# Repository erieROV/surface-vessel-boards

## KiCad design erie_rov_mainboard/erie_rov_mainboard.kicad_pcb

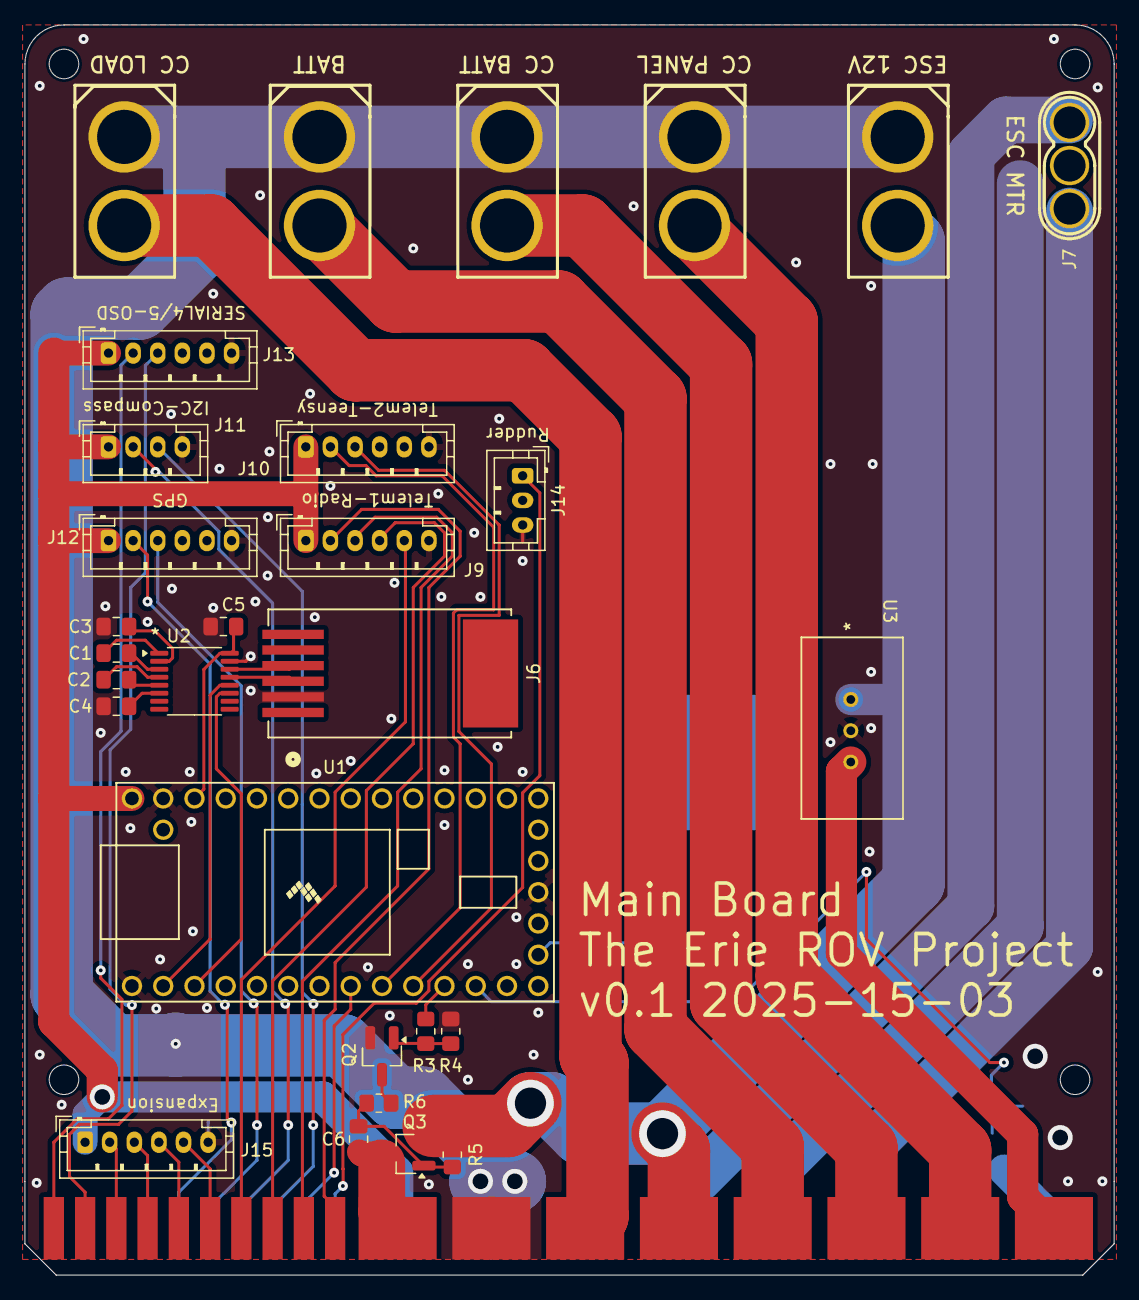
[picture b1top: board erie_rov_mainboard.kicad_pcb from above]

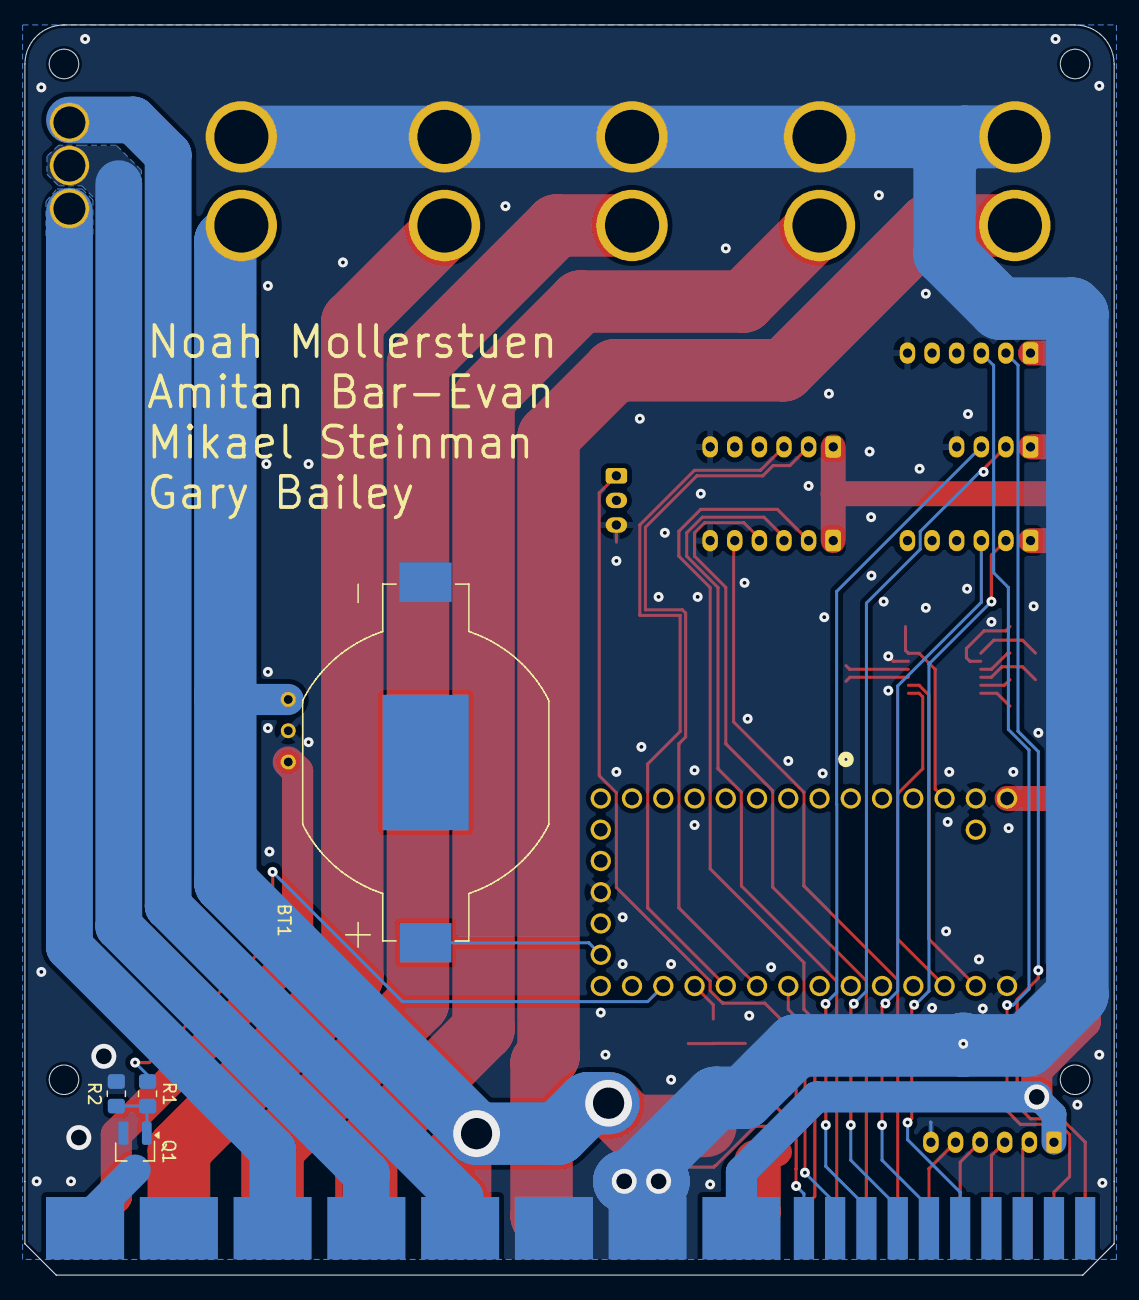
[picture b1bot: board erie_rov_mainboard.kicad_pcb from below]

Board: 2 copper layers, 88.5 x 101.6 mm, 34 parts (4 on the bottom side), 49 nets.

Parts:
BT1: BU2032SM-HD-G; BAT_BU2032SM-HD-G
C1, C2, C3, C4, C5: 0.1uF; C_0805_2012Metric_Pad1.18x1.45mm_HandSolder
C6: 10n; C_0805_2012Metric_Pad1.18x1.45mm_HandSolder
J1: 1761426-1; 1761426_1_CardEdge
J2: BATT; CONN-TH_XT60
J3: CC PANEL; CONN-TH_XT60
J4: CC BATT; CONN-TH_XT60
J5: CC LOAD; CONN-TH_XT60
J6: 855135002; CONN_85513-5002_MOL
J7: ESC MTR; CONN-TH_MR30-M
J8: ESC 12V; CONN-TH_XT60
J9: Telem1-Radio; JST_PH_B6B-PH-K_1x06_P2.00mm_Vertical
J10: Telem2-Teensy; JST_PH_B6B-PH-K_1x06_P2.00mm_Vertical
J11: I2C; JST_PH_B4B-PH-K_1x04_P2.00mm_Vertical
J12: GPS; JST_PH_B6B-PH-K_1x06_P2.00mm_Vertical
J13: SERIAL4/5-OSD; JST_PH_B6B-PH-K_1x06_P2.00mm_Vertical
J14: Rudder; JST_PH_B3B-PH-K_1x03_P2.00mm_Vertical
J15: Expansion; JST_PH_B6B-PH-K_1x06_P2.00mm_Vertical
Q1, Q2: FDV303N; SOT-23_Handsoldering
Q3: AO3401A; SOT-23_Handsoldering
R1, R3: 100; R_0805_2012Metric_Pad1.20x1.40mm_HandSolder
R2, R4, R5: 10K; R_0805_2012Metric_Pad1.20x1.40mm_HandSolder
R6: 1k; R_0805_2012Metric_Pad1.20x1.40mm_HandSolder
U1: Teensy4.0; Teensy40
U2: MAX3232CUE+T; TSSOP-16_4.4x5mm_P0.65mm
U3: TSR 2-2450; TSR 2-2450_TRP

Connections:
5V_AUX: J1.1, U3.3 (+VOUT)
+3.3V: C5.2, U1.31 (3V3), U2.16 (VCC)
+5V: J1.45 (P9), J9.1, J10.1, J11.1, J12.1, J13.1, J15.1, U1.33 (VIN)
+12V: J1.13 (P5), J8.2 (+), Q3.2 (S), R5.1, U3.1 (+VIN)
BATT_CC: J1.7 (P3), J4.2 (+)
BATT_SW: J1.10 (P4), J2.2 (+)
EXP_1: J1.32 (S8), J15.2
EXP_2: J1.31 (S7), J15.3
EXP_3: J1.30 (S6), J15.4
EXP_4: J1.29 (S5), J15.5
GND: BT1.-, C3.2, C4.1, C5.1, J1.19 (P7), J1.48 (P10), J1.51 (P11), J2.1 (-), J3.1 (-), J4.1 (-), J5.1 (-), J6.2, J8.1 (-), J9.6, J10.6, J11.4, J12.6, J13.6, J14.3, J15.6, Q1.2 (S), Q2.2 (S), R2.2, R4.2, U1.1 (GND), U1.17 (GND), U1.32 (GND), U2.15 (GND), U3.2 (GND)
GPS_RX: J1.40 (S16), J12.3
GPS_SCA: J1.42 (S18), J11.3
GPS_SCL: J1.41 (S17), J11.2
GPS_TX: J1.39 (S15), J12.2
LOAD_CC: J1.16 (P6), J5.2 (+)
MTR_B: J1.54 (P12), J7.1
MTR_G: J1.57 (P13), J7.2
MTR_W: J1.60 (P14), J7.3
unnamed: Q1.1 (G), R1.1, R2.1
unnamed: Q2.3 (D), R6.2
unnamed: Q2.1 (G), R3.1, R4.1
unnamed: C6.1, Q3.1 (G), R5.2, R6.1
unnamed: BT1.+, U1.15 (VBAT)
unnamed: C1.2, U2.1 (C1+)
unnamed: C1.1, U2.3 (C1-)
unnamed: C2.2, U2.4 (C2+)
unnamed: C2.1, U2.5 (C2-)
unnamed: J6.3, U2.13 (R1IN)
unnamed: J6.4, U2.14 (T1OUT)
unnamed: C3.1, U2.2 (V+)
unnamed: C4.2, U2.6 (V-)
OSD_RX: J1.33 (S9), J13.3
OSD_TX: J1.34 (S10), J13.2
PNL+: J1.4 (P2), J3.2 (+)
RDR_PWM: J1.44 (S20), J14.1
SCC_RX: U1.2 (0_RX1_CRX2_CS1), U2.12 (R1OUT)
SCC_TX: U1.3 (1_TX1_CTX2_MISO1), U2.11 (T1IN)
STRB_PWM: J1.43 (S19), U1.8 (6_OUT1D)
TELEM1_CTS: J1.27 (S3), J9.4
TELEM1_RTS: J1.28 (S4), J9.5
TELEM1_RX: J1.26 (S2), J9.3
TELEM1_TX: J1.25 (S1), J9.2
TELEM2_RX: J10.3, U1.10 (8_TX2_IN1)
TELEM2_TX: J10.2, U1.9 (7_RX2_OUT1A)
TELEM_GND: J1.66 (P16), Q1.3 (D)
TELEM_SW: R1.2, U1.12 (10_CS_MQSR)
VID_PWR: C6.2, J1.22 (P8), Q3.3 (D)
VTX_SW: R3.2, U1.11 (9_OUT1C)

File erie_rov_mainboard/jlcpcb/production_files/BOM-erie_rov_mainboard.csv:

Comment,Designator,Footprint,LCSC
BATT,"J2,J3,J4,J5,J8",CONN-TH_XT60,C98733
ESC MTR,J7,CONN-TH_MR30-M,C99873
1761426-1,J1,1761426_1_CardEdge,
MAX3232CUE+T,U2,TSSOP-16_4.4x5mm_P0.65mm,
AO3401A,Q3,SOT-23_Handsoldering,
0.1uF,C3,C_0805_2012Metric_Pad1.18x1.45mm_HandSolder,
Rudder,J14,JST_PH_B3B-PH-K_1x03_P2.00mm_Vertical,
Telem2-Teensy,J10,JST_PH_B6B-PH-K_1x06_P2.00mm_Vertical,
Expansion,J15,JST_PH_B6B-PH-K_1x06_P2.00mm_Vertical,
GPS,J12,JST_PH_B6B-PH-K_1x06_P2.00mm_Vertical,
100,R3,R_0805_2012Metric_Pad1.20x1.40mm_HandSolder,
Teensy4.0,U1,Teensy40,
I2C,J11,JST_PH_B4B-PH-K_1x04_P2.00mm_Vertical,
0.1uF,C1,C_0805_2012Metric_Pad1.18x1.45mm_HandSolder,
10K,R5,R_0805_2012Metric_Pad1.20x1.40mm_HandSolder,
Telem1-Radio,J9,JST_PH_B6B-PH-K_1x06_P2.00mm_Vertical,
FDV303N,Q2,SOT-23_Handsoldering,
0.1uF,C5,C_0805_2012Metric_Pad1.18x1.45mm_HandSolder,
10K,R4,R_0805_2012Metric_Pad1.20x1.40mm_HandSolder,
855135002,J6,CONN_85513-5002_MOL,
TSR 2-2450,U3,TSR 2-2450_TRP,
SERIAL4/5-OSD,J13,JST_PH_B6B-PH-K_1x06_P2.00mm_Vertical,
0.1uF,C2,C_0805_2012Metric_Pad1.18x1.45mm_HandSolder,
0.1uF,C4,C_0805_2012Metric_Pad1.18x1.45mm_HandSolder,
BU2032SM-HD-G,BT1,BAT_BU2032SM-HD-G,
10K,R2,R_0805_2012Metric_Pad1.20x1.40mm_HandSolder,
FDV303N,Q1,SOT-23_Handsoldering,
100,R1,R_0805_2012Metric_Pad1.20x1.40mm_HandSolder,
1k,R6,R_0805_2012Metric_Pad1.20x1.40mm_HandSolder,
10n,C6,C_0805_2012Metric_Pad1.18x1.45mm_HandSolder,

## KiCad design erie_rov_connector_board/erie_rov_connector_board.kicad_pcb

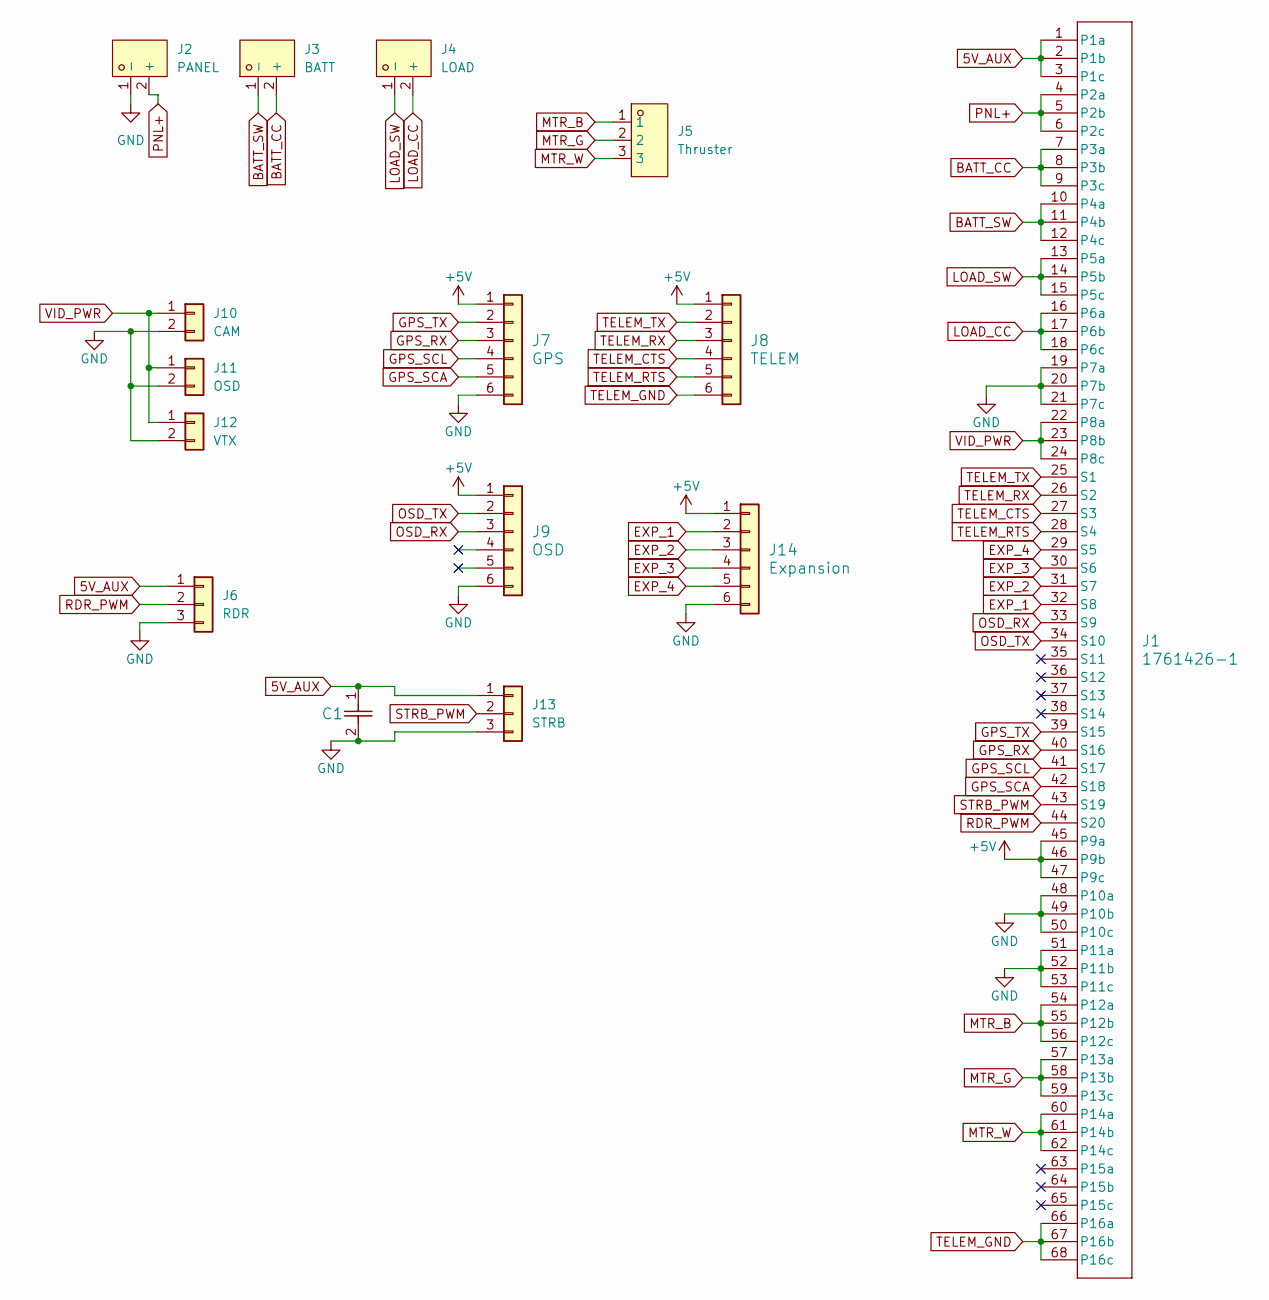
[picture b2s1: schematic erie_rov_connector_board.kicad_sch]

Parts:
C1: 16PK4700MEFC12.5X25; CAP_PK&slash_PZ_12P5X25_LOW_RUB
J1: 1761426-1; 1761426_1
J2: PANEL; CONN-TH_XT60; LCSC Part C98733
J3: BATT; CONN-TH_XT60; LCSC Part C98733
J4: LOAD; CONN-TH_XT60; LCSC Part C98733
J5: Thruster; CONN-TH_MR30-M; LCSC Part C99873
J6: RDR; JST_PH_B3B-PH-K_1x03_P2.00mm_Vertical; MPN B3B-XH-A(LF)(SN); Digi-Key_PN 455-2248-ND
J7: GPS; JST_PH_B6B-PH-K_1x06_P2.00mm_Vertical
J8: TELEM; JST_PH_B6B-PH-K_1x06_P2.00mm_Vertical
J9: OSD; JST_PH_B6B-PH-K_1x06_P2.00mm_Vertical
J10: CAM; JST_PH_B2B-PH-K_1x02_P2.00mm_Vertical; MPN B3B-XH-A(LF)(SN); Digi-Key_PN 455-2248-ND
J11: OSD; JST_PH_B2B-PH-K_1x02_P2.00mm_Vertical; MPN B3B-XH-A(LF)(SN); Digi-Key_PN 455-2248-ND
J12: VTX; JST_PH_B2B-PH-K_1x02_P2.00mm_Vertical; MPN B3B-XH-A(LF)(SN); Digi-Key_PN 455-2248-ND
J13: STRB; JST_PH_B3B-PH-K_1x03_P2.00mm_Vertical; MPN B3B-XH-A(LF)(SN); Digi-Key_PN 455-2248-ND
J14: Expansion; JST_PH_B6B-PH-K_1x06_P2.00mm_Vertical

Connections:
5V_AUX: C1.1, J1.1 (P1a), J1.2 (P1b), J1.3 (P1c), J6.1, J13.1
+5V: J1.45 (P9a), J1.46 (P9b), J1.47 (P9c), J7.1, J8.1, J9.1, J14.1
BATT_CC: J1.7 (P3a), J1.8 (P3b), J1.9 (P3c), J3.2 (+)
BATT_SW: J1.10 (P4a), J1.11 (P4b), J1.12 (P4c), J3.1 (-)
EXP_1: J1.32 (S8), J14.2
EXP_2: J1.31 (S7), J14.3
EXP_3: J1.30 (S6), J14.4
EXP_4: J1.29 (S5), J14.5
GND: C1.2, J1.19 (P7a), J1.20 (P7b), J1.21 (P7c), J1.48 (P10a), J1.49 (P10b), J1.50 (P10c), J1.51 (P11a), J1.52 (P11b), J1.53 (P11c), J2.1 (-), J6.3, J7.6, J9.6, J10.2, J11.2, J12.2, J13.3, J14.6
GPS_RX: J1.40 (S16), J7.3
GPS_SCA: J1.42 (S18), J7.5
GPS_SCL: J1.41 (S17), J7.4
GPS_TX: J1.39 (S15), J7.2
LOAD_CC: J1.16 (P6a), J1.17 (P6b), J1.18 (P6c), J4.2 (+)
LOAD_SW: J1.13 (P5a), J1.14 (P5b), J1.15 (P5c), J4.1 (-)
MTR_B: J1.54 (P12a), J1.55 (P12b), J1.56 (P12c), J5.1
MTR_G: J1.57 (P13a), J1.58 (P13b), J1.59 (P13c), J5.2
MTR_W: J1.60 (P14a), J1.61 (P14b), J1.62 (P14c), J5.3
OSD_RX: J1.33 (S9), J9.3
OSD_TX: J1.34 (S10), J9.2
PNL+: J1.4 (P2a), J1.5 (P2b), J1.6 (P2c), J2.2 (+)
RDR_PWM: J1.44 (S20), J6.2
STRB_PWM: J1.43 (S19), J13.2
TELEM_CTS: J1.27 (S3), J8.4
TELEM_GND: J1.66 (P16a), J1.67 (P16b), J1.68 (P16c), J8.6
TELEM_RTS: J1.28 (S4), J8.5
TELEM_RX: J1.26 (S2), J8.3
TELEM_TX: J1.25 (S1), J8.2
VID_PWR: J1.22 (P8a), J1.23 (P8b), J1.24 (P8c), J10.1, J11.1, J12.1

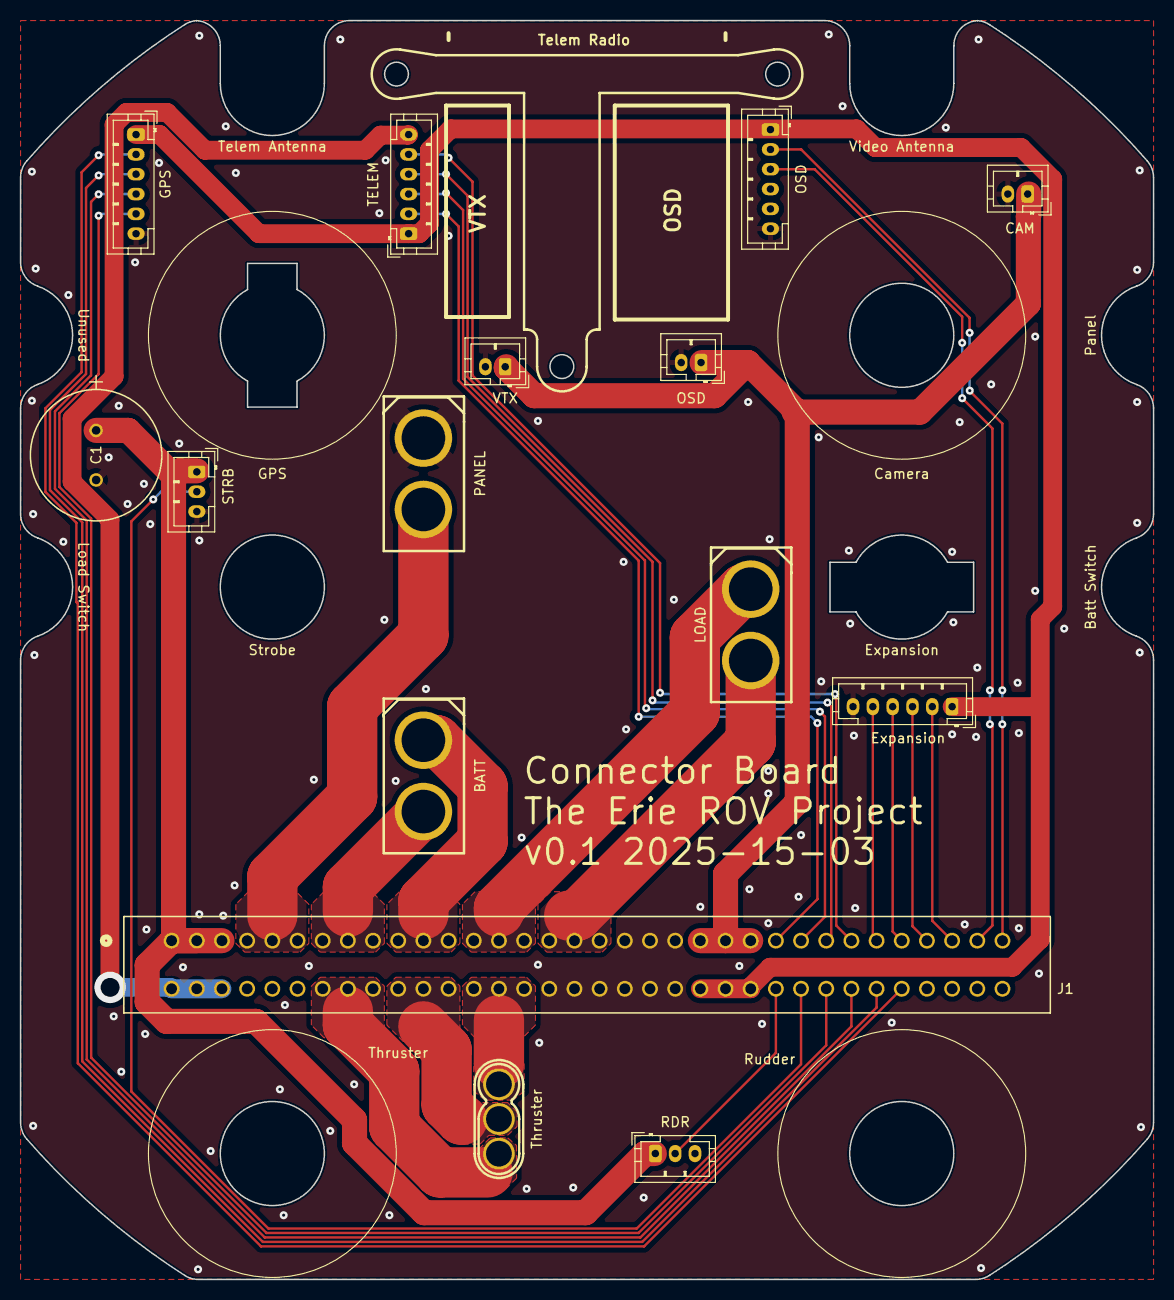
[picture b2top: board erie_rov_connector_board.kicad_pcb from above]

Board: 2 copper layers, 114.3 x 127.0 mm, 15 parts (0 on the bottom side), 29 nets.

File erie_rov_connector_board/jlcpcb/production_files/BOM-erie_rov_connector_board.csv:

Comment,Designator,Footprint,LCSC
PANEL,"J2,J3,J4",CONN-TH_XT60,C98733
Thruster,J5,CONN-TH_MR30-M,C99873
OSD,J9,JST_PH_B6B-PH-K_1x06_P2.00mm_Vertical,
Expansion,J14,JST_PH_B6B-PH-K_1x06_P2.00mm_Vertical,
OSD,J11,JST_PH_B2B-PH-K_1x02_P2.00mm_Vertical,
16PK4700MEFC12.5X25,C1,CAP_PK&slash_PZ_12P5X25_LOW_RUB,
CAM,J10,JST_PH_B2B-PH-K_1x02_P2.00mm_Vertical,
RDR,J6,JST_PH_B3B-PH-K_1x03_P2.00mm_Vertical,
1761426-1,J1,1761426_1,
GPS,J7,JST_PH_B6B-PH-K_1x06_P2.00mm_Vertical,
VTX,J12,JST_PH_B2B-PH-K_1x02_P2.00mm_Vertical,
TELEM,J8,JST_PH_B6B-PH-K_1x06_P2.00mm_Vertical,
STRB,J13,JST_PH_B3B-PH-K_1x03_P2.00mm_Vertical,

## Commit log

2025-03-14 v0.1
2025-03-19 Final changes before ordering v1.0
